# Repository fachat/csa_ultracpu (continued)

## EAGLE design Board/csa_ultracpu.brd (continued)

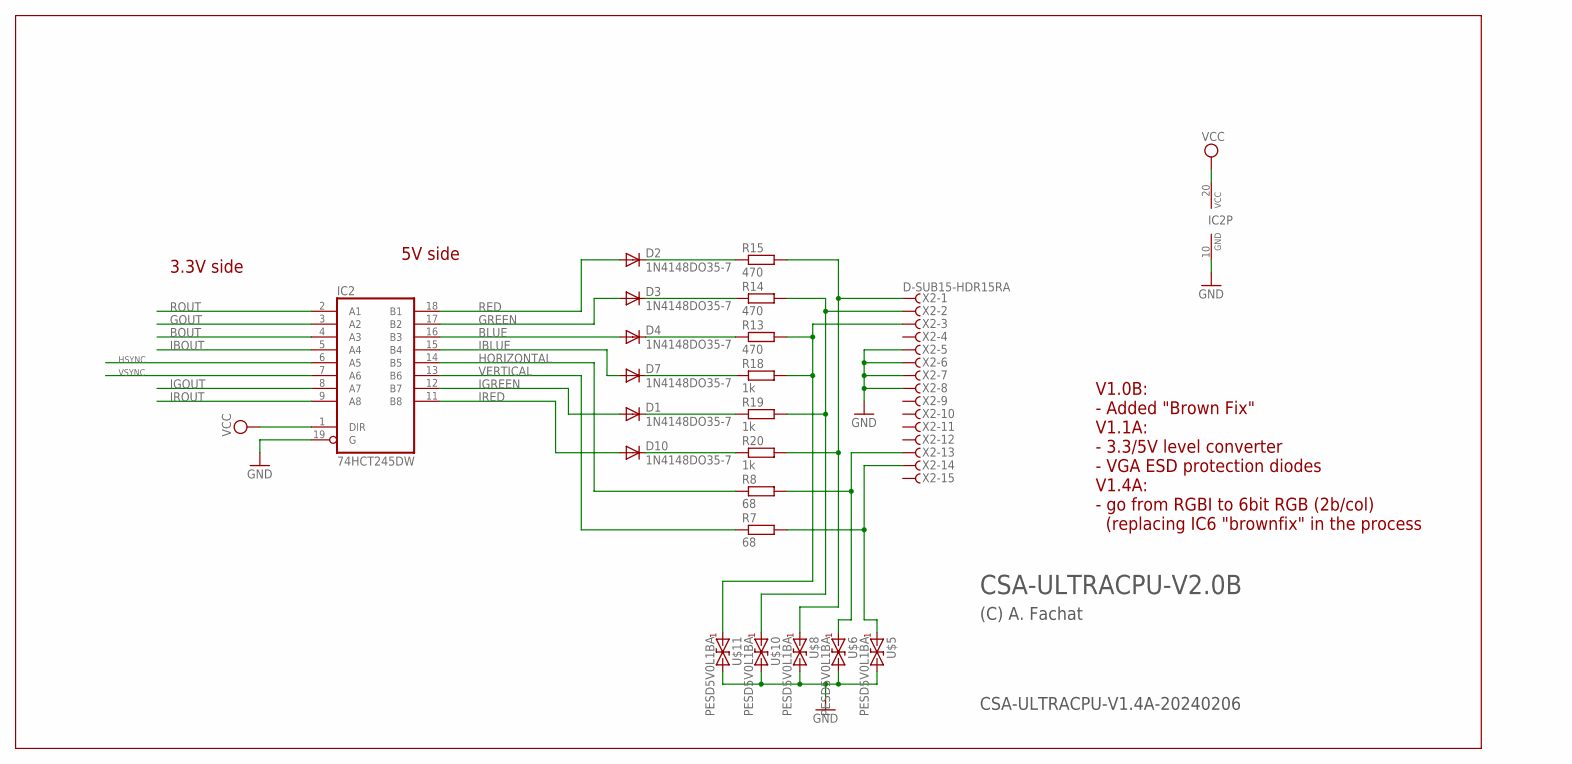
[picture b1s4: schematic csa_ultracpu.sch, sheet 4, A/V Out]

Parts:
D1, D2, D3, D4, D7, D10: 1N4148DO35-7; DO35-7
IC2: 74HCT245DW; SO20W
R7, R8: 68; 0204V
R13, R14, R15: 470; 0204V
R18, R19, R20: 1k; 0204V
U$5, U$6, U$8, U$10, U$11: PESD5V0L1BA; SOD323
X2: D-SUB15-HDR15RA; HDR15RA

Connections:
BLUE: D4.A, IC2.16 (B3)
BOUT: IC2.4 (A3); also elsewhere on the board
GND: IC2.10 (GND), IC2.19 (G), U$5.1 (2), U$6.1 (2), U$8.1 (2), U$10.1 (2), U$11.1 (2), X2.5, X2.6, X2.7, X2.8; also elsewhere on the board
GOUT: IC2.3 (A2); also elsewhere on the board
GREEN: D3.A, IC2.17 (B2)
HORIZONTAL: IC2.14 (B5), R8.1
HSYNC: IC2.6 (A5); also elsewhere on the board
IBLUE: D7.A, IC2.15 (B4)
IBOUT: IC2.5 (A4); also elsewhere on the board
IGOUT: IC2.8 (A7); also elsewhere on the board
IGREEN: D1.A, IC2.12 (B7)
IRED: D10.A, IC2.11 (B8)
IROUT: IC2.9 (A8); also elsewhere on the board
unnamed: D1.C, R19.1
unnamed: D7.C, R18.1
unnamed: R15.2, R20.2, U$8.2 (1), X2.1
unnamed: R14.2, R19.2, U$10.2 (1), X2.2
unnamed: R13.2, R18.2, U$11.2 (1), X2.3
unnamed: D10.C, R20.1
unnamed: R8.2, U$6.2 (1), X2.13
unnamed: R7.2, U$5.2 (1), X2.14
unnamed: D2.C, R15.1
unnamed: D3.C, R14.1
unnamed: D4.C, R13.1
RED: D2.A, IC2.18 (B1)
ROUT: IC2.2 (A1); also elsewhere on the board
VCC: IC2.1 (DIR), IC2.20 (VCC); also elsewhere on the board
VERTICAL: IC2.13 (B6), R7.1
VSYNC: IC2.7 (A6); also elsewhere on the board

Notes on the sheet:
CSA-ULTRACPU-V1.4A-20240206
CSA-ULTRACPU-V2.0B
(C) A. Fachat
V1.0B: - Added "Brown Fix" V1.1A: - 3.3/5V level converter - VGA ESD protection diodes V1.4A: - go from RGBI to 6bit RGB (2b/col) (replacing IC6 "brownfix" in the process
3.3V side
5V side

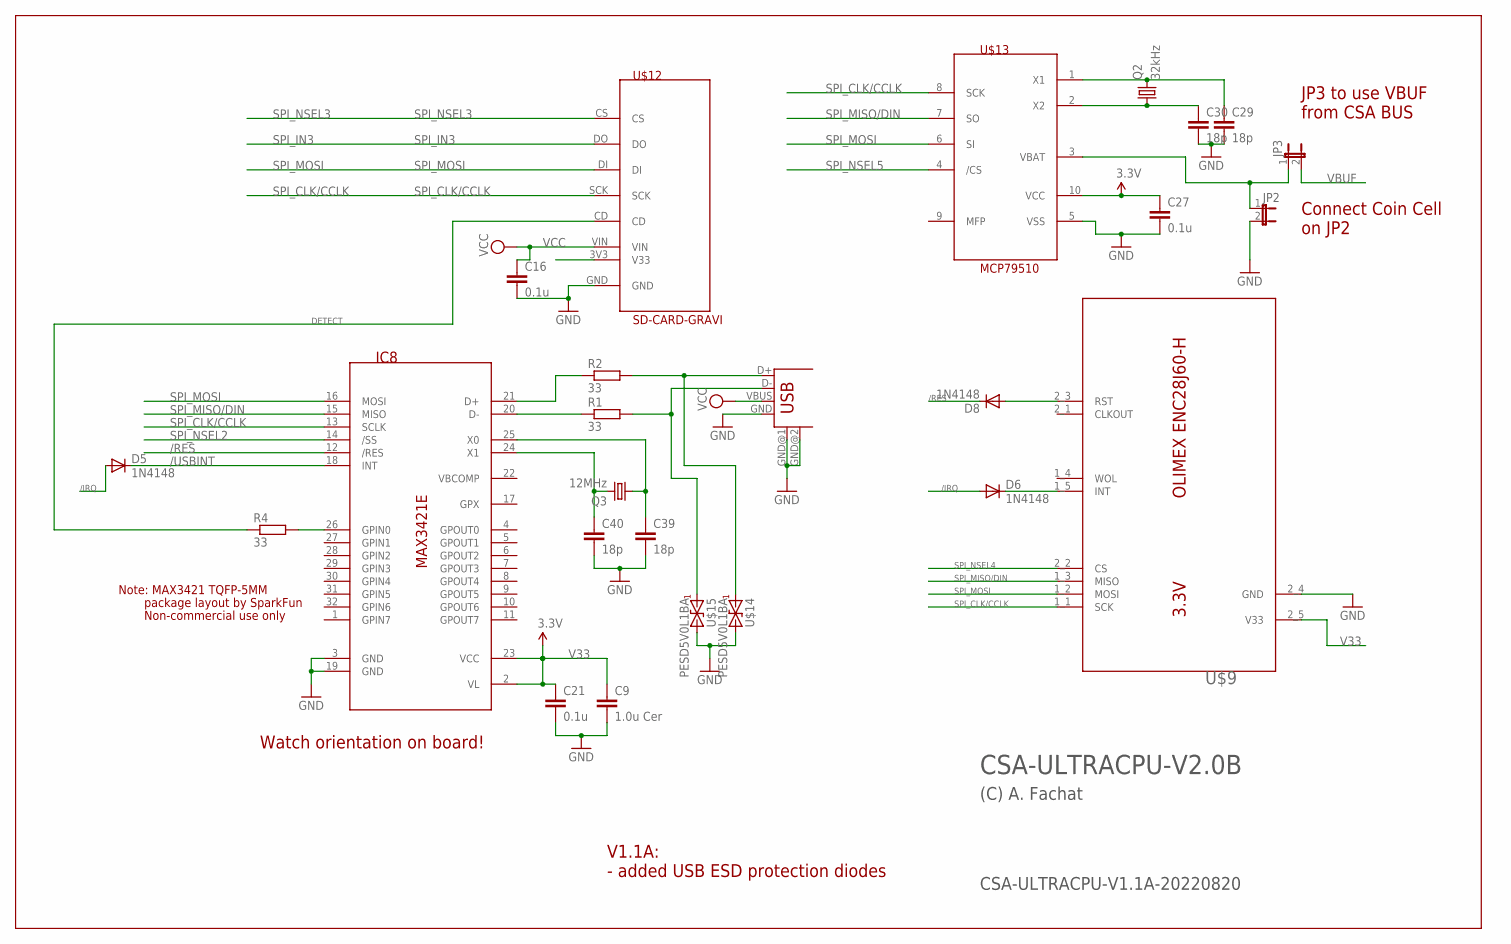
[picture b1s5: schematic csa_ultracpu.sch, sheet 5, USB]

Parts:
C9: 1.0u Cer; C0603
C16, C21, C27: 0.1u; C0603
C29, C30, C39, C40: 18p; C0603
D5, D6, D8: 1N4148; D-5
IC8: MAX3421E; TQFP32-5MM
JP2, JP3: JP1E; JP1
Q2: 32kHz; TC26H
Q3: 12MHz; HC49/S
R1, R2, R4: 33; 0204/7
U$9: ETHOLIENC
U$12: SD-CARD-GRAVI; GRAVITECH-SDCARD
U$13: MCP79510; MSOP10
U$14, U$15: PESD5V0L1BA; SOD323
USB1: USB-A-H

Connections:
12MHZ: C40.1, IC8.24 (X1), Q3.2
/IRQ: D5.A, D6.A; also elsewhere on the board
/RES: D8.C, IC8.12 (/RES); also elsewhere on the board
/USBINT: D5.C, IC8.18 (INT)
DETECT: R4.1, U$12.CD
FOO: U$12.3V3 (V33)
GND: C9.2, C16.2, C21.2, C27.2, C29.2, C30.2, C39.2, C40.2, IC8.3 (GND), IC8.19 (GND), JP2.2, U$9.2_4 (GND), U$12.GND, U$13.5 (VSS), U$14.1 (2), U$15.1 (2), USB1.GND, USB1.GND@1 (GND), USB1.GND@2 (GND); also elsewhere on the board
unnamed: IC8.20 (D-), R1.1
unnamed: IC8.21 (D+), R2.1
unnamed: C29.1, Q2.2, U$13.1 (X1)
unnamed: D6.C, U$9.1_5 (INT)
unnamed: R2.2, U$14.2 (1), USB1.D+
unnamed: R1.2, U$15.2 (1), USB1.D-
unnamed: IC8.26 (GPIN0), R4.2
unnamed: C30.1, Q2.1, U$13.2 (X2)
unnamed: D8.A, U$9.2_3 (RST)
unnamed: C39.1, IC8.25 (X0), Q3.1
SPI_CLK/CCLK: IC8.13 (SCLK), U$9.1_1 (SCK), U$12.SCK, U$13.8 (SCK); also elsewhere on the board
SPI_IN3: U$12.DO; also elsewhere on the board
SPI_MISO/DIN: IC8.15 (MISO), U$9.1_3 (MISO), U$13.7 (SO); also elsewhere on the board
SPI_MOSI: IC8.16 (MOSI), U$9.1_2 (MOSI), U$12.DI, U$13.6 (SI); also elsewhere on the board
SPI_NSEL2: IC8.14 (/SS); also elsewhere on the board
SPI_NSEL3: U$12.CS; also elsewhere on the board
SPI_NSEL4: U$9.2_2 (CS); also elsewhere on the board
SPI_NSEL5: U$13.4 (/CS); also elsewhere on the board
V33: C9.1, C21.1, C27.1, IC8.2 (VL), IC8.23 (VCC), U$9.2_5 (V33), U$13.10 (VCC); also elsewhere on the board
VBAT: JP2.1, JP3.1, U$13.3 (VBAT)
VBUF: JP3.2; also elsewhere on the board
VCC: C16.1, U$12.VIN, USB1.VBUS; also elsewhere on the board

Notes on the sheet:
Watch orientation on board!
Note: MAX3421 TQFP-5MM
Non-commercial use only
package layout by SparkFun
CSA-ULTRACPU-V1.1A-20220820
CSA-ULTRACPU-V2.0B
(C) A. Fachat
Connect Coin Cell on JP2
JP3 to use VBUF from CSA BUS
V1.1A: - added USB ESD protection diodes

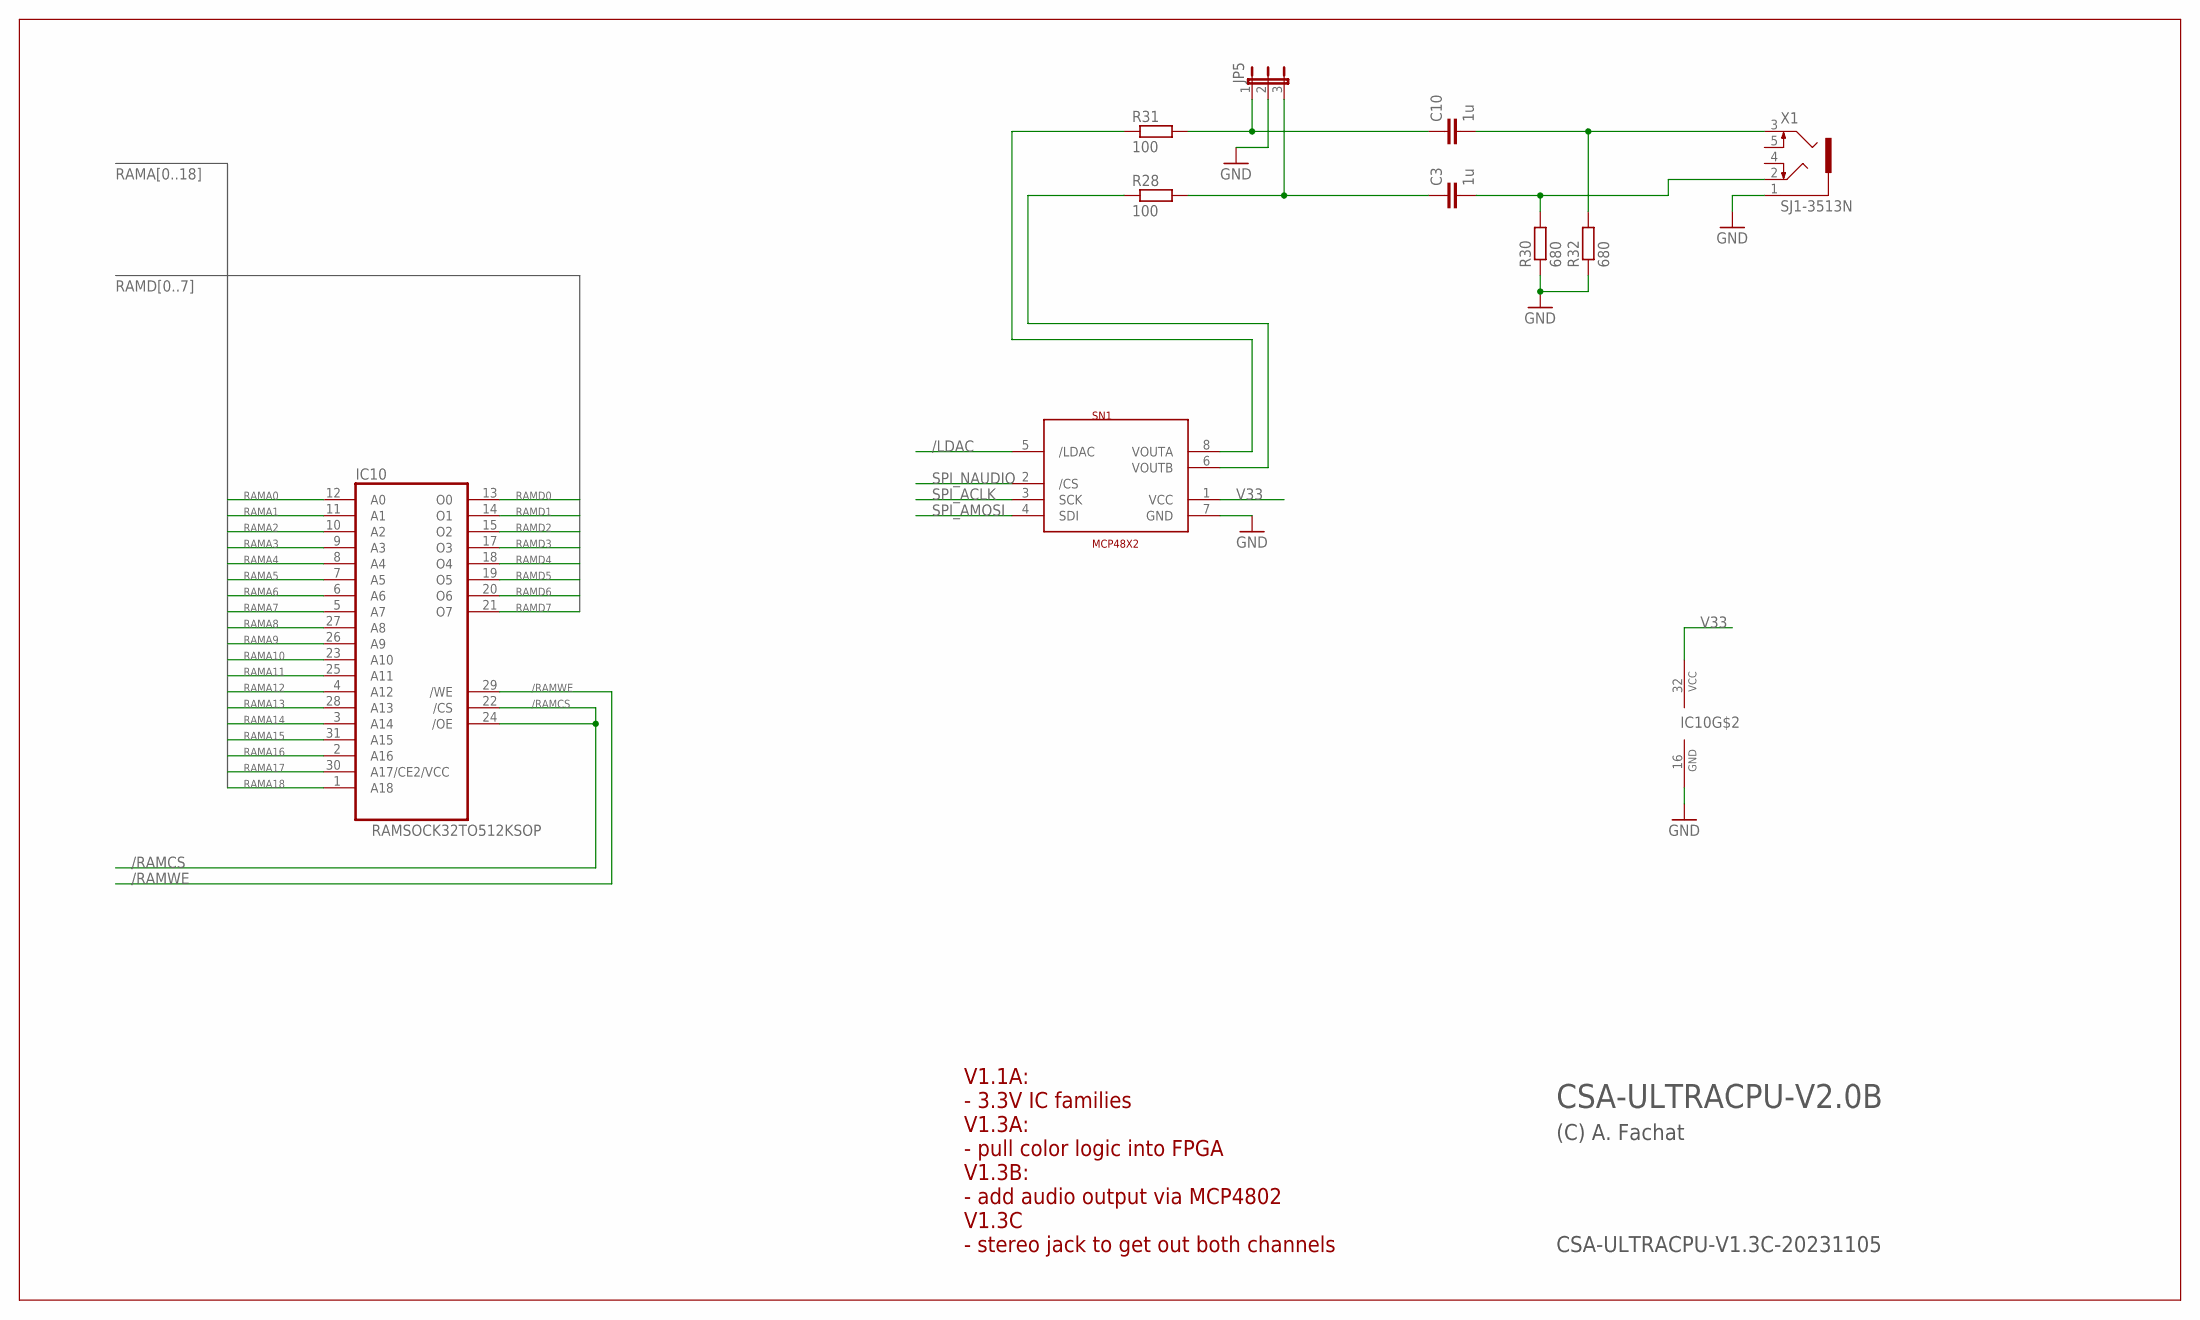
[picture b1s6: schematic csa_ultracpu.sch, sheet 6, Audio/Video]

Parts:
C3, C10: 1u; C050-025X075
IC10: RAMSOCK32TO512KSOP; SOP32
JP5: JP2E; JP2
R28, R31: 100; 0204V
R30, R32: 680; 0204V
SN1: MCP48X2; SOIC8
X1: SJ1-3513N; 1503_09

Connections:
/LDAC: SN1.5 (/LDAC); also elsewhere on the board
/RAMCS: IC10.22 (/CS), IC10.24 (/OE); also elsewhere on the board
/RAMWE: IC10.29 (/WE); also elsewhere on the board
GND: IC10.16 (GND), JP5.2, R30.1, R32.1, SN1.7 (GND), X1.1; also elsewhere on the board
unnamed: R28.1, SN1.6 (VOUTB)
unnamed: C3.2, R30.2, X1.2
unnamed: R31.1, SN1.8 (VOUTA)
unnamed: C10.1, JP5.1, R31.2
unnamed: C10.2, R32.2, X1.3
unnamed: C3.1, JP5.3, R28.2
RAMA0: IC10.12 (A0); also elsewhere on the board
RAMA1: IC10.11 (A1); also elsewhere on the board
RAMA2: IC10.10 (A2); also elsewhere on the board
RAMA3: IC10.9 (A3); also elsewhere on the board
RAMA4: IC10.8 (A4); also elsewhere on the board
RAMA5: IC10.7 (A5); also elsewhere on the board
RAMA6: IC10.6 (A6); also elsewhere on the board
RAMA7: IC10.5 (A7); also elsewhere on the board
RAMA8: IC10.27 (A8); also elsewhere on the board
RAMA9: IC10.26 (A9); also elsewhere on the board
RAMA10: IC10.23 (A10); also elsewhere on the board
RAMA11: IC10.25 (A11); also elsewhere on the board
RAMA12: IC10.4 (A12); also elsewhere on the board
RAMA13: IC10.28 (A13); also elsewhere on the board
RAMA14: IC10.3 (A14); also elsewhere on the board
RAMA15: IC10.31 (A15); also elsewhere on the board
RAMA16: IC10.2 (A16); also elsewhere on the board
RAMA17: IC10.30 (A17/CE2/VCC); also elsewhere on the board
RAMA18: IC10.1 (A18); also elsewhere on the board
RAMD0: IC10.13 (O0); also elsewhere on the board
RAMD1: IC10.14 (O1); also elsewhere on the board
RAMD2: IC10.15 (O2); also elsewhere on the board
RAMD3: IC10.17 (O3); also elsewhere on the board
RAMD4: IC10.18 (O4); also elsewhere on the board
RAMD5: IC10.19 (O5); also elsewhere on the board
RAMD6: IC10.20 (O6); also elsewhere on the board
RAMD7: IC10.21 (O7); also elsewhere on the board
SPI_ACLK: SN1.3 (SCK); also elsewhere on the board
SPI_AMOSI: SN1.4 (SDI); also elsewhere on the board
SPI_NAUDIO: SN1.2 (/CS); also elsewhere on the board
V33: IC10.32 (VCC), SN1.1 (VCC); also elsewhere on the board

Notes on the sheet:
CSA-ULTRACPU-V1.3C-20231105
CSA-ULTRACPU-V2.0B
(C) A. Fachat
V1.1A: - 3.3V IC families V1.3A: - pull color logic into FPGA V1.3B: - add audio output via MCP4802 V1.3C - stereo jack to get out both channels

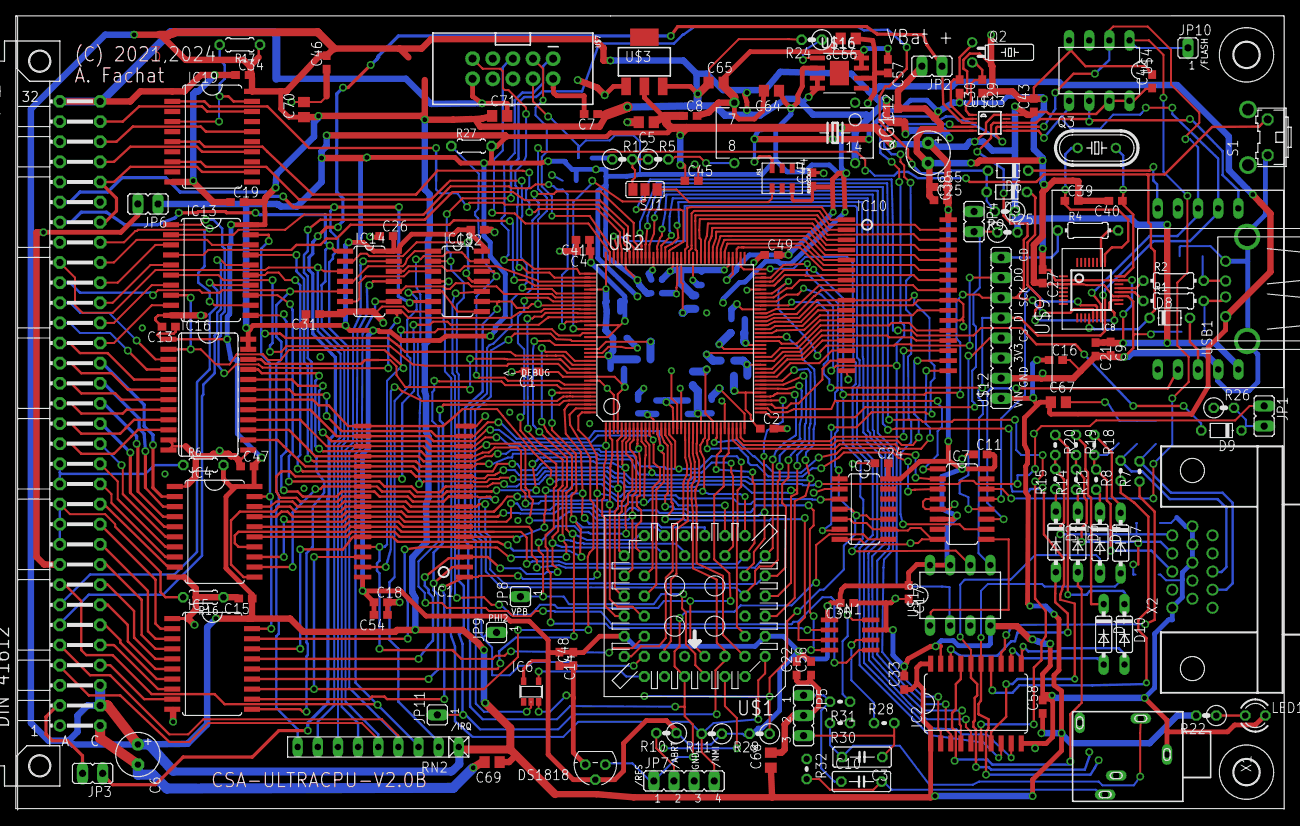
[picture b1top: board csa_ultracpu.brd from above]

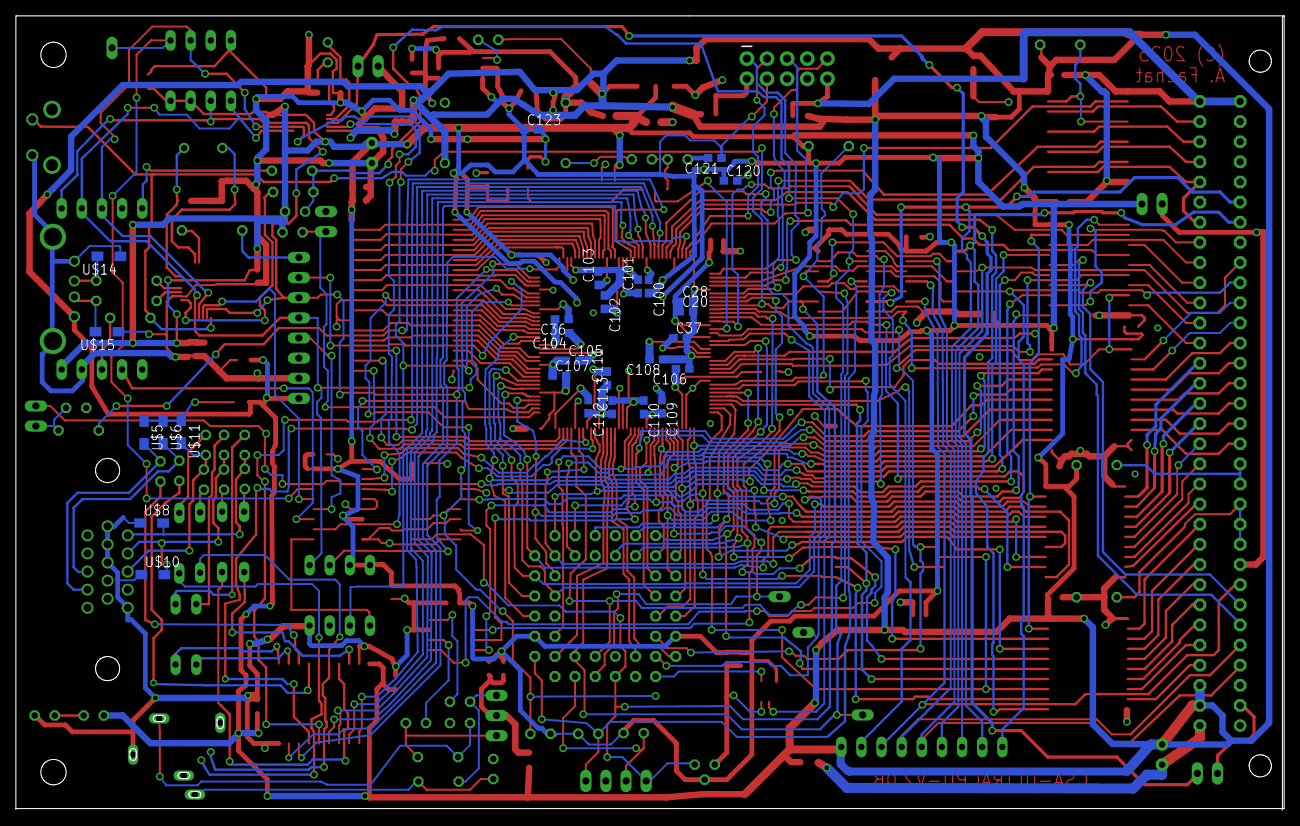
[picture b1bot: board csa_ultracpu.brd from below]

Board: 4 copper layers, 160.0 x 100.2 mm, 175 parts (28 on the bottom side), 219 nets.

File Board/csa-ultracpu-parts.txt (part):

Partlist

Exported from csa_ultracpu.sch at 4/17/22 9:51 PM

EAGLE Version 6.4.0 Copyright (c) 1988-2013 CadSoft

Assembly variant: 

Part     Value              Device             Package          Library          Sheet

C1       0.1u               C-EUC0603          C0603            rcl              3
C2       0.1u               C-EUC0603          C0603            rcl              3
C3       0.1u               C-EUC0603          C0603            rcl              3
C4       0.1u               C-EUC0603          C0603            rcl              3
C5       47u                CPOL-EUE5-6        E5-6             rcl              3
C6       47u                CPOL-EUE2.5-6      E2,5-6           rcl              3
C7       100n               C-EUC0603          C0603            rcl              3
C8       100n               C-EUC0603          C0603            rcl              3
C9       1.0u Cer           C-EUC0603          C0603            rcl              5
C10      1u                 C-EUC0603          C0603            rcl              3
C11      1u                 C-EUC0603          C0603            rcl              3
C12      0.1u               C-EUC0603          C0603            rcl              3
C13      0.1u               C-EUC0603          C0603            rcl              3
C14      0.1u               C-EUC0603          C0603            rcl              3
C15      0.1u               C-EUC0603          C0603            rcl              3
C16      0.1u               C-EUC0603          C0603            rcl              5
C17      0.1u               C-EUC0603          C0603            rcl              3
C18      0.1u               C-EUC0603          C0603            rcl              3
C19      0.1u               C-EUC0603          C0603            rcl              3
C20      0.1u               C-EUC0603          C0603            rcl              3
C21      0.1u               C-EUC0603          C0603            rcl              5
C22      0.1u               C-EUC0603          C0603            rcl              3
C23      0.1u               C-EUC0603          C0603            rcl              3
C24      0.1u               C-EUC0603          C0603            rcl              3
C25      0.1u               C-EUC0603          C0603            rcl              3
C26      47u                CPOL-EUE2.5-6      E2,5-6           rcl              3
C27      0.1u               C-EUC0603          C0603            rcl              5
C28      22u                CPOL-EUE2.5-6      E2,5-6           rcl              3
C29      18p                C-EUC0603          C0603            rcl              5
C30      18p                C-EUC0603          C0603            rcl              5
C31      0.1u               C-EUC0603          C0603            rcl              3
C32      0.1u               C-EUC0603          C0603            rcl              3
C33      0.1u               C-EUC0603          C0603            rcl              3
C34      0.1u               C-EUC0603          C0603            rcl              3
C35      0.1u               C-EUC0603          C0603            rcl              3
C36      22u                CPOL-EUE2.5-6      E2,5-6           rcl              3
C37      22u                CPOL-EUE2.5-6      E2,5-6           rcl              3
C38      22u                CPOL-EUE2.5-6      E2,5-6           rcl              3
C39      18p                C-EUC0603          C0603            rcl              5
C40      18p                C-EUC0603          C0603            rcl              5
C41      0.1u               C-EUC0603          C0603            rcl              3
C42      0.1u               C-EUC0603          C0603            rcl              3
C43      0.1u               C-EUC0603          C0603            rcl              3
C44      0.1u               C-EUC0603          C0603            rcl              3
C45      0.1u               C-EUC0603          C0603            rcl              3
C46      0.1u               C-EUC0603          C0603            rcl              3
C47      0.1u               C-EUC0603          C0603            rcl              3
C48      0.1u               C-EUC0603          C0603            rcl              3
C49      1u                 C-EUC0603          C0603            rcl              3
C50      1u                 C-EUC0603          C0603            rcl              3
C51      1u                 C-EUC0603          C0603            rcl              3
C52      0.1u               C-EUC0603          C0603            rcl              3
C53      1u                 C-EUC0603          C0603            rcl              3
C54      1u                 C-EUC0603          C0603            rcl              3
C55      1u                 C-EUC0603          C0603            rcl              3
C56      1u                 C-EUC0603          C0603            rcl              3
C57      22u                CPOL-EUE2.5-6      E2,5-6           rcl              3
C58      0.1u               C-EUC0603          C0603            rcl              3
D1       1N4148DO35-7       1N4148DO35-7       DO35-7           diode            4
D2       1N4148DO35-7       1N4148DO35-7       DO35-7           diode            4
D3       1N4148DO35-7       1N4148DO35-7       DO35-7           diode            4
D4       1N4148DO35-7       1N4148DO35-7       DO35-7           diode            4
D5       1N4148             DIODE-D-5          D-5              diode            5
D6       1N4148             DIODE-D-5          D-5              diode            5
D7       1N4148DO35-7       1N4148DO35-7       DO35-7           diode            4
D8       1N4148             DIODE-D-5          D-5              diode            5
IC1      RAMSOCK32TO512KSOP RAMSOCK32TO512KSOP SOP32            csa              2
IC2      74LS245DW          74LS245DW          SO20W            74xx-eu          4
IC3      74LS245DW          74LS245DW          SO20W            74xx-eu          1
IC4      74LS245DW          74LS245DW          SO20W            74xx-eu          1
IC5      74LS245DW          74LS245DW          SO20W            74xx-eu          1
IC6      74ACT138D          74ACT138D          SO16             74xx-eu          4
IC7      74LS245DW          74LS245DW          SO20W            74xx-eu          6
IC8      MAX3421E           MAX3421E           TQFP32-5MM       csa              5
IC9      74LS166D           74LS166D           SO16             74xx-eu          6
IC10     RAMSOCK32TO512KSOP RAMSOCK32TO512KSOP SOP32            csa              6
IC11     74HCT574D          74HCT574D          SO20W            74xx-eu          6
IC12     74HCT574D          74HCT574D          SO20W            74xx-eu          6
IC13     74HCT244DW         74HCT244DW         SO20W            74xx-eu          1
IC14     74HCT14D           74HCT14D           SO14             74xx-eu          1
IC15     74HCT157D          74HCT157D          SO16             74xx-eu          6
IC18     74LS06D            74LS06D            SO14             74xx-eu          1
IC19     74HCT244DW         74HCT244DW         SO20W            74xx-eu          1
J1                          FLOPPY-4350211     350211           con-amp          3
JP1                         JP1E               JP1              jumper           2
JP2                         JP1E               JP1              jumper           5
JP3                         JP1E               JP1              jumper           5
JP7                         JP4E               JP4              jumper           2
LED1                        LED3MM             LED3MM           led              3
P1       CSABUS             CSABUS             CSABUS           csa              1
Q2       32kHz              CRYSTALTC26H       TC26H            crystal          5
Q3       12MHz              CRYSTALHC49S       HC49/S           crystal          5
QG1      50MHz              CRYSTAL_RES-SG51   SG51             crystal          2
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
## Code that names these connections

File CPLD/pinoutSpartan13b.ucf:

#
# csa_ultracpu 1.3b
#
## NET VD<0>	LOC=P142 | IOSTANDARD=LVCMOS33 |PULLUP;
## NET VD<0>	LOC=P142 | IOSTANDARD=LVCMOS33 | DRIVE=16;

NET VD<0>	LOC=P47 | IOSTANDARD = LVTTL | TNM = "vd_tnm";	# RAMD0
NET VD<1>	LOC=P46 | IOSTANDARD = LVTTL | TNM = "vd_tnm";
NET VD<2>	LOC=P39 | IOSTANDARD = LVTTL | TNM = "vd_tnm";
NET VD<3>	LOC=P33 | IOSTANDARD = LVTTL | TNM = "vd_tnm";
NET VD<4>	LOC=P34 | IOSTANDARD = LVTTL | TNM = "vd_tnm";
NET VD<5>	LOC=P35 | IOSTANDARD = LVTTL | TNM = "vd_tnm";
NET VD<6>	LOC=P48 | IOSTANDARD = LVTTL | TNM = "vd_tnm";
NET VD<7>	LOC=P51 | IOSTANDARD = LVTTL | TNM = "vd_tnm";

NET VA<0>	LOC=P50 | IOSTANDARD = LVTTL;	# RAMA0
NET VA<1>	LOC=P55 | IOSTANDARD = LVTTL;
NET VA<2>	LOC=P58 | IOSTANDARD = LVTTL;
NET VA<3>	LOC=P60 | IOSTANDARD = LVTTL;	# RAMA3/M0
NET VA<4>	LOC=P61 | IOSTANDARD = LVTTL;
NET VA<5>	LOC=P66 | IOSTANDARD = LVTTL;	# RAMA5/VS1
NET VA<6>	LOC=P75 | IOSTANDARD = LVTTL;
NET VA<7>	LOC=P79 | IOSTANDARD = LVTTL;
NET VA<8>	LOC=P78 | IOSTANDARD = LVTTL;
NET VA<9>	LOC=P69 | IOSTANDARD = LVTTL;	# RAMA9/VS0
NET VA<10>	LOC=P57 | IOSTANDARD = LVTTL;
NET VA<11>	LOC=P62 | IOSTANDARD = LVTTL;	# RAMA11/VS2
NET VA<12>	LOC=P81 | IOSTANDARD = LVTTL;
NET VA<13>	LOC=P80 | IOSTANDARD = LVTTL;
NET VA<14>	LOC=P83 | IOSTANDARD = LVTTL;
NET VA<15>	LOC=P87 | IOSTANDARD = LVTTL;
NET VA<16>	LOC=P85 | IOSTANDARD = LVTTL;
NET VA<17>	LOC=P84 | IOSTANDARD = LVTTL;
NET VA<18>	LOC=P88 | IOSTANDARD = LVTTL;

NET FA<15>	LOC=P140 | IOSTANDARD = LVTTL;	# FA15
NET FA<16>	LOC=P141 | IOSTANDARD = LVTTL;
NET FA<17>	LOC=P143 | IOSTANDARD = LVTTL;
NET FA<18>	LOC=P144 | IOSTANDARD = LVTTL;	# FA18/HSWAP
NET FA<19>	LOC=P101 | IOSTANDARD = LVTTL;

NET D<0>	LOC=P2 | IOSTANDARD = LVTTL | TNM = "d_tnm";		# D0
NET D<1>	LOC=P1 | IOSTANDARD = LVTTL | TNM = "d_tnm";
NET D<2>	LOC=P14 | IOSTANDARD = LVTTL | TNM = "d_tnm";
NET D<3>	LOC=P5 | IOSTANDARD = LVTTL | TNM = "d_tnm";
NET D<4>	LOC=P12 | IOSTANDARD = LVTTL | TNM = "d_tnm";
NET D<5>	LOC=P8 | IOSTANDARD = LVTTL | TNM = "d_tnm";
NET D<6>	LOC=P9 | IOSTANDARD = LVTTL | TNM = "d_tnm";
NET D<7>	LOC=P6 | IOSTANDARD = LVTTL | TNM = "d_tnm";

NET A<0>	LOC=P17 | IOSTANDARD = LVTTL;	# A0
NET A<1>	LOC=P56 | IOSTANDARD = LVTTL;
NET A<2>	LOC=P45 | IOSTANDARD = LVTTL;
NET A<3>	LOC=P43 | IOSTANDARD = LVTTL;
NET A<4>	LOC=P44 | IOSTANDARD = LVTTL;
NET A<5>	LOC=P40 | IOSTANDARD = LVTTL;
NET A<6>	LOC=P41 | IOSTANDARD = LVTTL;
NET A<7>	LOC=P26 | IOSTANDARD = LVTTL;
NET A<8>	LOC=P30 | IOSTANDARD = LVTTL;
NET A<9>	LOC=P10 | IOSTANDARD = LVTTL;
NET A<10>	LOC=P11 | IOSTANDARD = LVTTL;
NET A<11>	LOC=P142 | IOSTANDARD = LVTTL;
NET A<12>	LOC=P127 | IOSTANDARD = LVTTL;
NET A<13>	LOC=P139 | IOSTANDARD = LVTTL;
NET A<14>	LOC=P119 | IOSTANDARD = LVTTL;
NET A<15>	LOC=P131 | IOSTANDARD = LVTTL;

NET VPA		LOC=P24 | IOSTANDARD = LVTTL;	# VPA
NET VDA		LOC=P22 | IOSTANDARD = LVTTL;	# VDA

NET NIOSEL	LOC=P134 | IOSTANDARD = LVTTL;	# /IOSEL

NET NVRAMSEL	LOC=P59 | IOSTANDARD = LVTTL;	# /RAMCS/M1
NET NFRAMSEL	LOC=P120 | IOSTANDARD = LVTTL;	# /FRAMSEL
NET RAMRWB	LOC=P82 | IOSTANDARD = LVTTL;	# /RAMWE

NET GRAPHIC	LOC=P137 | IOSTANDARD = LVTTL;	# GRAPHIC

NET HSYNC	LOC=P99 | IOSTANDARD = LVTTL;	# HSYNC
NET VSYNC	LOC=P98 | IOSTANDARD = LVTTL;	# VSYNC
NET PET_VSYNC	LOC=P92 | IOSTANDARD = LVTTL;	# PET_VSYNC

NET Q50M	LOC=P123 | IOSTANDARD = LVTTL;	# 50M
NET Q50M	BUFG=CLK;
NET Q50M 	PERIOD=20;

#NET DBG		LOC=P137 | IOSTANDARD = LVTTL;
NET RWB		LOC=P124 | IOSTANDARD = LVTTL;	#LOC=P134;	# R/-W
NET NRES	LOC=P117 | IOSTANDARD = LVTTL;	# /RES
NET NRES	BUFG=SR;

NET NIRQ 	LOC=P23 | IOSTANDARD = LVTTL;

#NET MLB		LOC=P21 | IOSTANDARD = LVTTL;
NET VPB			LOC=P7 | IOSTANDARD = LVTTL;
NET E			LOC=P21 | IOSTANDARD = LVTTL;
#NET MX			LOC=P24 | IOSTANDARD = LVTTL;

NET PHI2		LOC=P126 | IOSTANDARD = LVTTL;

NET RDY			LOC=P32 | IOSTANDARD = LVTTL;

NET EXTIO		LOC=P115 | IOSTANDARD = LVTTL;
NET IOINH		LOC=P111 | IOSTANDARD = LVTTL;
NET NMEMSEL		LOC=P112 | IOSTANDARD = LVTTL;
NET nbe_out		LOC=P132 | IOSTANDARD = LVTTL;	# /BE_OUT
NET nbe_dout		LOC=P133 | IOSTANDARD = LVTTL;	# /BE_DOUT
NET be_in		LOC=P118 | IOSTANDARD = LVTTL;
NET SYNC		LOC=P121 | IOSTANDARD = LVTTL;

NET CPHI2		LOC=P114 | IOSTANDARD = LVTTL;
NET C2PHI2		LOC=P104 | IOSTANDARD = LVTTL;
NET C8PHI2		LOC=P102 | IOSTANDARD = LVTTL;

NET PXL_OUT<0>		LOC=P93 | IOSTANDARD = LVTTL | PERIOD=40;	# IBOUT
NET PXL_OUT<1>		LOC=P94 | IOSTANDARD = LVTTL | PERIOD=40;	# BOUT
NET PXL_OUT<2>		LOC=P74 | IOSTANDARD = LVTTL | PERIOD=40;	# IGOUT
NET PXL_OUT<3>		LOC=P95 | IOSTANDARD = LVTTL | PERIOD=40;	# GOUT
NET PXL_OUT<4>		LOC=P105 | IOSTANDARD = LVTTL | PERIOD=40;	# IROUT
NET PXL_OUT<5>		LOC=P97 | IOSTANDARD = LVTTL | PERIOD=40;	# ROUT

NET SPI_SELA		LOC=P38 | IOSTANDARD = LVTTL;	# SPISELA/CSO_B
NET SPI_SELB		LOC=P29 | IOSTANDARD = LVTTL;
NET SPI_SELC		LOC=P27 | IOSTANDARD = LVTTL;

NET SPI_OUT		LOC=P64 | IOSTANDARD = LVTTL;	# SPI_MOSI
NET SPI_CLK		LOC=P100 | IOSTANDARD = LVTTL;	# SPI_CLK/CCLK
NET SPI_IN1		LOC=P65 | IOSTANDARD = LVTTL; # | PULLUP;	# SPI_MISO/DIN

NET SPI_IN3		LOC=P67 | IOSTANDARD = LVTTL | PULLUP;

NET SPI_NAUDIO		LOC=P116 | IOSTANDARD = LVTTL;
NET SPI_ACLK		LOC=P16 | IOSTANDARD = LVTTL;
NET SPI_AMOSI		LOC=P15 | IOSTANDARD = LVTTL;
NET NLDAC		LOC=P138 | IOSTANDARD = LVTTL;

#NET INIT_B		LOC=P | IOSTANDARD = LVTTL;

INST "NFRAMSEL"					TNM = "ram_tnm";
INST "NVRAMSEL"					TNM = "ram_tnm";
INST "RAMRWB"						TNM = "ram_tnm";

INST "SPI_CLK"						BUFG=CLK | TNM = "dotclk_tnm";
#INST "clocky/memclk_int"		BUFG=CLK;
INST "clocky/dotclk_int_1"		BUFG=CLK | TNM = "dotclk_tnm";
INST "q50m"							TNM = "qclk_tnm";
#INST "viccy/vid_fetch"			BUFG=CLK | TNM = "vidfetch_tnm";
TIMESPEC "ts_dotclk" = FROM "qclk_tnm" TO "dotclk_tnm" 3 ns DATAPATHONLY;
#TIMESPEC "ts_vidfetch" = FROM "qclk_tnm" to "vidfetch_tnm" 3 ns DATAPATHONLY;
TIMESPEC "ts_ram" = FROM "qclk_tnm" TO "ram_tnm" 4 ns DATAPATHONLY;

TIMESPEC "ts_vwrite"	= FROM "d_tnm" to "vd_tnm" 7 ns DATAPATHONLY;

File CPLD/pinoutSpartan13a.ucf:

#
## NET VD<0>	LOC=P142 | IOSTANDARD=LVCMOS33 |PULLUP;
## NET VD<0>	LOC=P142 | IOSTANDARD=LVCMOS33 | DRIVE=16;

NET VD<0>	LOC=P83;
NET VD<1>	LOC=P77;
NET VD<2>	LOC=P75;
NET VD<3>	LOC=P74;
NET VD<4>	LOC=P76;
NET VD<5>	LOC=P81;
NET VD<6>	LOC=P23;
NET VD<7>	LOC=P25;

NET VA<0>	LOC=P82;
NET VA<1>	LOC=P85;
NET VA<2>	LOC=P86;
NET VA<3>	LOC=P88;
NET VA<4>	LOC=P92;
NET VA<5>	LOC=P94;
NET VA<6>	LOC=P97;
NET VA<7>	LOC=P98;
NET VA<8>	LOC=P105;
NET VA<9>	LOC=P96;
NET VA<10>	LOC=P87;
NET VA<11>	LOC=P93;
NET VA<12>	LOC=P104;
NET VA<13>	LOC=P103;
NET VA<14>	LOC=P123;
NET VA<15>	LOC=P122;
NET VA<16>	LOC=P106;
NET VA<17>	LOC=P117;
NET VA<18>	LOC=P125;

NET FA<15>	LOC=P34;
NET FA<16>	LOC=P70;
NET FA<17>	LOC=P113;	#P71;
NET FA<18>	LOC=P53;
NET FA<19>	LOC=P142;

NET D<0>	LOC=P52;
NET D<1>	LOC=P51;
NET D<2>	LOC=P50;
NET D<3>	LOC=P3;	#P44;
NET D<4>	LOC=P43;
NET D<5>	LOC=P40;
NET D<6>	LOC=P26;	#P39;
NET D<7>	LOC=P35;

NET A<0>	LOC=P69;
NET A<1>	LOC=P68;
NET A<2>	LOC=P67;
NET A<3>	LOC=P66;
NET A<4>	LOC=P101;	#P63;
NET A<5>	LOC=P95;	#62;	#95;
NET A<6>	LOC=P120;	#P60;
NET A<7>	LOC=P59;
NET A<8>	LOC=P58;
NET A<9>	LOC=P111;	#P57;
NET A<10>	LOC=P56;
NET A<11>	LOC=P31;
NET A<12>	LOC=P48;
NET A<13>	LOC=P47;
NET A<14>	LOC=P41;
NET A<15>	LOC=P38;

NET VPA		LOC=P29;
NET VDA		LOC=P6;

NET NIOSEL	LOC=P33;

NET NVRAMSEL	LOC=P91;
NET NFRAMSEL	LOC=P112;
NET RAMRWB	LOC=P8;

NET GRAPHIC	LOC=P36;

NET HSYNC	LOC=P15;
NET VSYNC	LOC=P16;
NET PET_VSYNC	LOC=P7;

NET Q50M	LOC=P128;
NET Q50M	BUFG=CLK;
NET Q50M PERIOD=20;

NET RWB		LOC=P129;
NET NRES	LOC=P107;
NET NRES	BUFG=SR;

NET PHI2_IO	LOC=P116;	# UNUSED!!!
NET PHI2_IO	BUFG=CLK;

##NET MLB		LOC=P21;
##NET VPB		LOC=P22;
NET E			LOC=P141;
##NET MX			LOC=P24;

NET SPI_IN3		LOC=P78;

NET NFLASH		LOC=P21;
NET SPI_NSEL2		LOC=P143;
#NET SPI_NSEL3		LOC=P3;
NET SPI_NSEL4		LOC=P4;

#NET SPI_NSEL5		LOC=P26;

##NET MEMCLK		BUFG=CLK;
##NET MEMCLK		NOREDUCE;
#
##NET PHI2		BUFG=CLK;
NET PHI2		LOC=P2;

NET RDY			LOC=P136;

NET EXTIO		LOC=P12;
NET IOINH		LOC=P10;
NET NMEMSEL		LOC=P132;
NET nbe_out		LOC=P32;
NET nbe_dout		LOC=P139;
NET be_in		LOC=P18;
NET SYNC		LOC=P135;

NET CPHI2		LOC=P134;
NET C2PHI2		LOC=P130;
NET C8PHI2		LOC=P131;

#NET COLORLD		LOC=P54;
#NET COLORLD2		LOC=P16;

#NET DENA	LOC=P5;
#NET PXLLD		LOC=P126;
#NET NSRLOAD		LOC=P14;
#NET nchromaddr		LOC=P140;
#NET DCLK	LOC=P20;	# SRCLK

NET PXL_OUT<0>	LOC=P14;	# ROUT IOUT
NET PXL_OUT<1>	LOC=P126;# GOUT BOUT
NET PXL_OUT<3>	LOC=P20;	# BOUT ROUT
NET PXL_OUT<2>	LOC=P140;# IOUT GOUT
#
#NET SPI_OUT		LOC=P44;	#P22;
#NET SPI_CLK		LOC=P71;	#P17;
#NET NFLASH		LOC=P39;	#P21;
#NET SPI_IN1		LOC=P63;	#P89;

NET SPI_OUT		LOC=P22;
NET SPI_CLK		LOC=P17;
NET NFLASH		LOC=P21;
NET SPI_IN1		LOC=P89;

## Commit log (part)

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2022-04-23 update README, add pictures
2022-04-23 updated readmes
2022-04-23 Trying to fix a strange non-reset on power-up behaviour
2022-04-23 clean up README: remove 8x96 mapping, hires; update boot menu
2022-04-24 VHDL cleanup of unused signals
2022-04-24 shrink image file size
2022-05-14 sync 1Mhz bus and CPU trigger; re-enable 8296
2022-05-15 update ROM
2022-05-15 add benchmark code
2022-05-15 adapt tests for the Ultra-PET
2023-03-25 updated pinout to compile for Spartan
2023-07-19 GRAPHICS now goes to a level shifting inverter
2023-07-19 obsolete IC7 by storing character index in the FPGA
2023-07-20 deprecating IC9, IC11 on ultracpu 1.2b by moving stuff into the FPGA
2023-07-23 obsolete IC12, IC15 by pulling into FPGA
2023-07-23 cleanup code
2023-07-23 more cleanup
2023-07-23 work on a timing issue between pixel output and hsync;
2023-07-25 cleanup, make video interface simpler
2023-08-01 move I/O around to free FPGA bot prom lines
2023-08-07 change layout, add bin and mcs FPGA images, and mkbin.sh script
2023-08-11 new pinout for ucpu 1.3b
2023-08-11 added signals to ucpu pinout
2023-08-11 pinout for 1.3b
2023-08-11 re-route vpb
2023-08-14 started working on requirements for Viccy-II
2023-08-15 work on Viccy II reqs2
2023-08-15 working on Viccy-II
2023-08-15 work on Viccy-II
2023-08-15 more work on Viccy-II - broken
2023-08-16 work on Viccy attribute timing
2023-08-24 more work on pixel pipeline
2023-08-24 fixed pixel timing!
2023-08-25 introduce separate attr and crom pointers as Viccy registers
2023-09-01 work on reading the registers, and auto-increase index
2023-09-02 introduce VGA Canvas
2023-09-10 work on h border timing
2023-09-10 stabillilize border
2023-09-23 more work on ground up timing rework
2023-09-23 more work on h timing
2023-09-24 horizontal timing complete w/ r1,r25.4,r44
2023-09-25 add upet compat mode, disp enable
2023-09-25 first refactor of vertical timing/border
2023-09-26 cleanup; move interlace/double/80 to r8; vert timing
2023-09-26 vshift almost working
2023-09-26 vertical timing, incl. v_shift
2023-09-26 implemented h_shift
2023-09-26 implement address offset r27
2023-09-26 fix hires address calculation
2023-09-26 started working on raster interrupt - but current test hw has no irq output...
2023-09-27 works with ultracpu 1.3b
2023-09-27 small fixes/reverts
2023-09-27 compare regs with VDC from https://www.c64-wiki.de/wiki/VDC, add TODOs
2023-09-28 small fixes, first demo
2023-10-01 working on the demo
2023-10-01 fixed some init bugs, reverse r24 shift
2023-10-07 make attr. colour shift w/ horizontal smooth scroll
2023-10-07 alternatve video address works
2023-10-15 mapper simplification
2023-10-15 change top clock to q50m/dotclk instead of memclk
2023-10-15 switch timing to q50m in ipl
2023-10-15 fix vborder / vtiming
2023-10-16 Fix vertical border timing
2023-10-16 timing...
2023-10-16 pin constraints to LVTTL
2023-10-17 clarify vramrwb - now half qclk behind select
2023-10-17 cleanup video code
2023-10-17 add Init_b to pinout desc
2023-10-17 fix number of written viccy registers in demo (was triggering alt address)
2023-10-17 more work on vborder
2023-10-17 fix blinking
2023-10-18 simplify clocky, add maxskew constraint
2023-10-18 simplify top; add system jitter attribute on qclk
2023-10-18 fetch attrib only when needed
2023-10-18 add from-to time constraint in ucf
2023-10-19 make vert scroll and changing charsets work
2023-10-19 double possible # of char lines; fix border bug in smooth horizontal scroll
2023-10-19 add maxdelay constraint to dotclk
2023-10-19 fix resetable address counters, add resetable rc counter
2023-10-19 adapt to r46
2023-10-21 prep demo for resetable counters
2023-10-21 upet compat for vid addr; move rasterline counter to r30/31
2023-10-21 add hires demo
2023-10-21 fix one-off starting border in 40col mode
2023-10-21 start on multicolour
2023-10-21 multicolour mode working
2023-10-22 first sprite (display only, no read yet)
2023-10-22 sprite colours
2023-10-23 work on sprites
2023-10-23 more work on sprites
2023-10-24 more work on sprites, expand, reg access, data fetch
2023-10-24 more work on sprites; over/under raster, over/under border
2023-10-24 vertical raster / border timing
2023-10-24 sprite y
2023-10-25 sprite multicolur
2023-10-25 move sprite fetch out of raster's way
2023-10-25 8 sprites; fix sprite fetch; fine coordinate mode
2023-10-25 add demos; adjust sprite bitmap to c64 format; on border bit does not affect on raster
2023-10-25 add FPGA config flash image
2023-10-25 fine tune sprite limits
2023-10-29 update demos
2023-11-02 video clean, start working on DAC
2023-11-02 Ethernet test code
2023-11-02 integrate DAC fetch
2023-11-02 small optimization in mapper
2023-11-02 more work on DAC integration
2023-11-03 more work on dac
2023-11-03 basic dma engine to send out data via dac
2023-11-04 DMA engine for DAC working
2023-11-05 work on DAC
2023-11-05 cleanup dac, update test
2023-11-05 FPGA config ROM, addl. test
2023-11-05 make DAC DMA len full VRAM size
2023-11-06 dac dma interrupt
2023-11-06 work on DAC DMA IRQ and restart
2023-11-08 FPGA flash image
2023-11-08 DAC documentation
2023-11-08 implement memory-mapped viccy register option
2023-11-09 implement Viccy R22 & R23
2023-11-09 refactor hshift, work on collisions
2023-11-11 sprite-border collision
2023-11-11 sprite-raster and sprite-sprite collisions
2023-11-11 add R22/R23 effects to demo
2023-11-11 implemented - not tested yet - sprite/border/raster/sprite interrupts
2023-11-12 refactored sprite handling into own file
2023-11-12 add note on refactoring
2023-11-12 fix missing sprite-border interrupt
2023-11-26 re-org of Viccy registers
2023-11-26 option to use xxx as window to CS/A bus IO area
2023-11-26 enable read out of Micro-PET control registers
2023-11-27 update FPGA config ROM
2023-12-11 update doc about Viccy registers
2023-12-11 shorten bus phi2 a bit on write cycles, to allow for better hold times; required by CSA_NETUSB it seems
2023-12-12 newer images
2023-12-12 update Video description
2023-12-12 link DAC description in README
2023-12-12 editor updates
2023-12-14 update ipl code to colour-boot again
2023-12-14 fix x/y swap in 40 col extended editor
2023-12-14 refactor boot code further out
2023-12-17 fix autostart bug introduced in last patch
2023-12-17 make USB keyboard scan during boot screen - but not used yet
2023-12-17 experimental support for USB keyboards on BASIC4
2023-12-20 update usb code to handle Ctrl-C
2023-12-21 separate out video map into own control register
2023-12-21 avoid reading MAPREG (upet compat)
2023-12-21 revert to VDRIVE interrupt on boot (upet compat)
2023-12-21 add name/copyright on boot screen
2023-12-29 make keyboard scan work even in absence of USB
2024-01-04 update memory map in README
2024-02-03 implement dual mono for DAC
2024-02-03 update DAC docs
2024-02-03 updated some constraints, video timing for 70Mhz - but not working
2024-02-05 initial dry-run spartan6
2024-02-06 implement palette in viccy-ii for 2/2/2 RGB
2024-02-09 add palette support
2024-02-09 add alternate palette support
2024-02-09 new fpga config prom image
2024-02-12 re-factor FPGA code such that it can more easily be reused in other systems
2024-02-12 cleanup
2024-03-22 first work
2024-03-22 work
2024-03-24 more work
2024-03-24 more work - boots, bleeds bank0 writes into vram
2024-03-25 vram timing ok; init issues (boot to 8032 before fpga load); ieee irq issues still; leftmost pixel error
2024-03-25 incremental
2024-03-25 stable timing, but no CPU reaction
2024-03-25 fix ipl write; delay cpu phi2 to stabilize timing
2024-03-25 back to 50m
2024-03-26 registering A in mapper works at 50m
2024-03-26 more clock phases
2024-03-26 working with 12MHz
2024-03-26 ok 12M; improve timing
2024-03-27 first light on 70Mhz
2024-03-27 even runs at 17MHz...- going into FPGA placement territory it seems
2024-03-27 still ok but better scope trigger
2024-03-27 add time constraint for VRAM write
2024-03-27 update center position; update ROM
2024-03-27 make vertical offset work
2024-03-28 fix LDAC back to original
2024-03-29 SPI changes
2024-03-29 improve docs, fix virtpet
2024-03-29 make sure SD cards work by adding pullup to SD-Card specfici MISO signal
2024-04-21 pinout 1.4a /ulti 1.0a; 1mhz cpu clk timing
2024-04-21 fix bus timing
2024-04-25 IPL waits a time before using spi_clk as the FPGA seems to switch if off way after initial config is done...
2024-04-29 fix R25 bitwise shift logic
2024-04-29 fix vertical position; sprite fetch
2024-04-29 update boot ROM, updemo
2024-04-29 update updemo; try to fix left border start in 40 col mode (8 pix too late)
2024-04-30 fix 40 col left border start
2024-04-30 add missing boot rom src files, new images
2024-05-05 add uPet CPLD shell
2024-05-06 add binary rom image for FPGA
2024-05-23 fix upet shell for non-inverted graphics input; dacfile for new clock speed
2024-05-24 add shell for UltraCPU / UltiPET
2024-06-17 separate out ROM, CPLD/FPGA, update readme
2024-06-17 update board to 2.0b from internal repo
2024-06-19 add missing images
2024-06-20 add link to family repo
2024-06-26 handle (no) sub repos
2024-12-13 more work on r2.1a
2024-12-15 more work on r2.1a - only bom xls is missing/outdated
2024-12-25 add Flash ROM type prints on PCB
2024-12-26 first try on BOM
2024-12-26 ultracpu 2.1a
2024-12-28 work on BOM
2024-12-31 fix bom
2025-01-17 r2.1a-fixes
2026-06-02 start r2.2a, moving from VGA to HDMI
